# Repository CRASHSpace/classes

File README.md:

classes
=======

a repo for materials and examples relating to our classes

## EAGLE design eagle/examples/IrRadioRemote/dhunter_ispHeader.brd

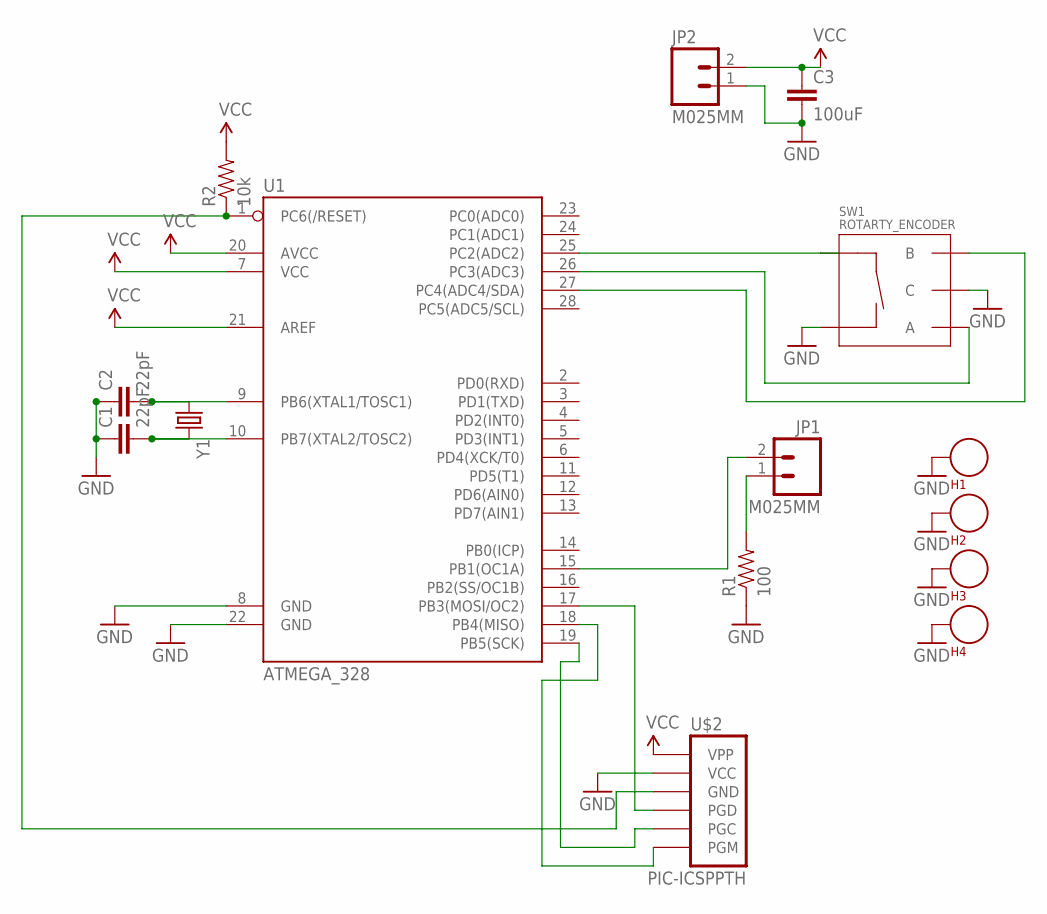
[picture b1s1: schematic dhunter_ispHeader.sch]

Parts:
C1, C2: 22pF; CAP-PTH-SMALLEZ
C3: 100uF; CAP-PTH-SMALLEZ
H1, H2, H3, H4: SEW_HOLE; SIMPLE_HOLE
JP1, JP2: M025MM; SCREWTERMINAL-5MM-2
R1: 100; AXIAL-0.3EZ
R2: 10k; AXIAL-0.3EZ
SW1: ROTARTY_ENCODER; ROTARY_ENC_PLAIN
U1: ATMEGA_328; DIL28-3
U$2: PIC-ICSPPTH; MOLEX-1X6
Y1: CRYSTALHC49US; HC49US

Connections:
GND: C1.1, C2.1, C3.2, H1.P$1, H2.P$1, H3.P$1, H4.P$1, JP2.1, R1.P$1 (1), SW1.C, SW1.SW-, U1.8 (GND), U1.22 (GND), U$2.5 (VCC)
unnamed: SW1.SW+, U1.25 (PC2(ADC2))
unnamed: U1.17 (PB3(MOSI/OC2)), U$2.3 (PGD)
unnamed: U1.19 (PB5(SCK)), U$2.2 (PGC)
unnamed: C1.2, U1.10 (PB7(XTAL2/TOSC2)), Y1.2
unnamed: C2.2, U1.9 (PB6(XTAL1/TOSC1)), Y1.1
unnamed: JP1.2, U1.15 (PB1(OC1A))
unnamed: JP1.1, R1.P$2 (2)
unnamed: R2.P$1 (1), U1.1 (PC6(/RESET)), U$2.4 (GND)
unnamed: U1.18 (PB4(MISO)), U$2.1 (PGM)
ROTA: SW1.A, U1.26 (PC3(ADC3))
ROTB: SW1.B, U1.27 (PC4(ADC4/SDA))
VCC: C3.1, JP2.2, R2.P$2 (2), U1.7 (VCC), U1.20 (AVCC), U1.21 (AREF), U$2.6 (VPP)

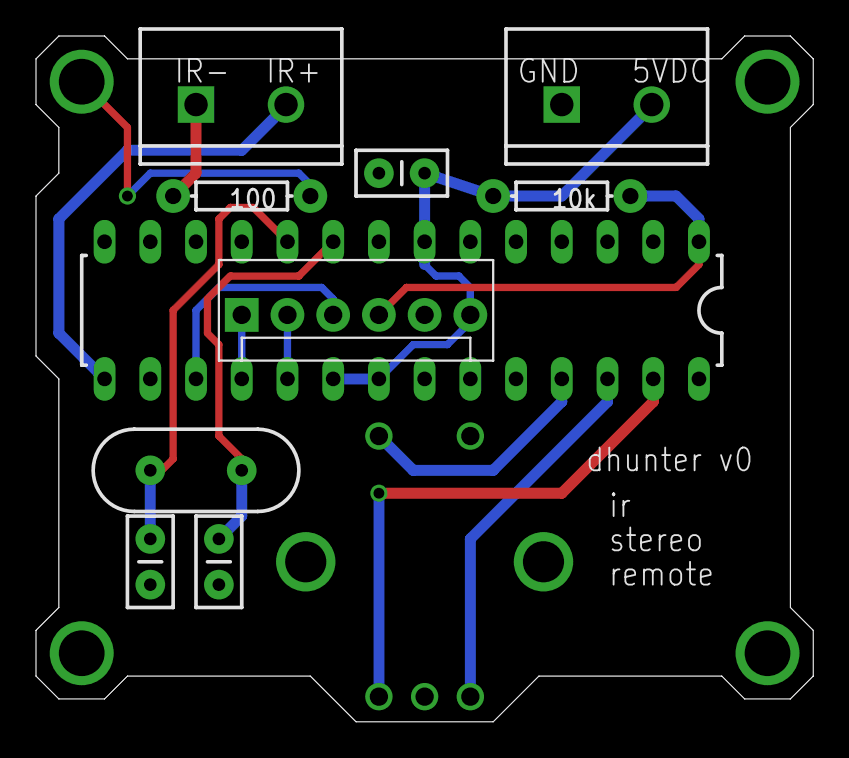
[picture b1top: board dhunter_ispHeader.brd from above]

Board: 2 copper layers, 43.2 x 38.1 mm, 15 parts (1 on the bottom side), 13 nets.

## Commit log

2012-12-13 adding syllabus
2012-12-13 hello
2012-12-13 naim
2012-12-13 john
2012-12-18 updated with new slides link
2013-01-29 adding new directories for each class
2013-01-29 adding gitignore for mac garbage
2013-01-30 added some examples
2013-01-31 adding code and fritzing
2013-01-31 adding slides
2013-02-01 new irrecod code
2013-02-01 machine tutorial
2013-02-01 moved fritzing file
2013-02-14 updating code to be more friendly, better comments, and delays for serial output
2013-03-29 added for first intro to processing class
2013-03-29 moved notes for better organization
2013-03-29 adding code from first class
2013-03-29 updated from what we actually covered in class
2013-03-29 adding a noAudio version for webexport
2014-01-15 added wildwood class
2014-02-13 adding eagle class
2014-02-15 updarted per class

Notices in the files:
parts and their libraries:
SparkFun-Electromechanical: Licensing: CC v3.0 Share-Alike You are welcome to use this library for commercial purposes.
